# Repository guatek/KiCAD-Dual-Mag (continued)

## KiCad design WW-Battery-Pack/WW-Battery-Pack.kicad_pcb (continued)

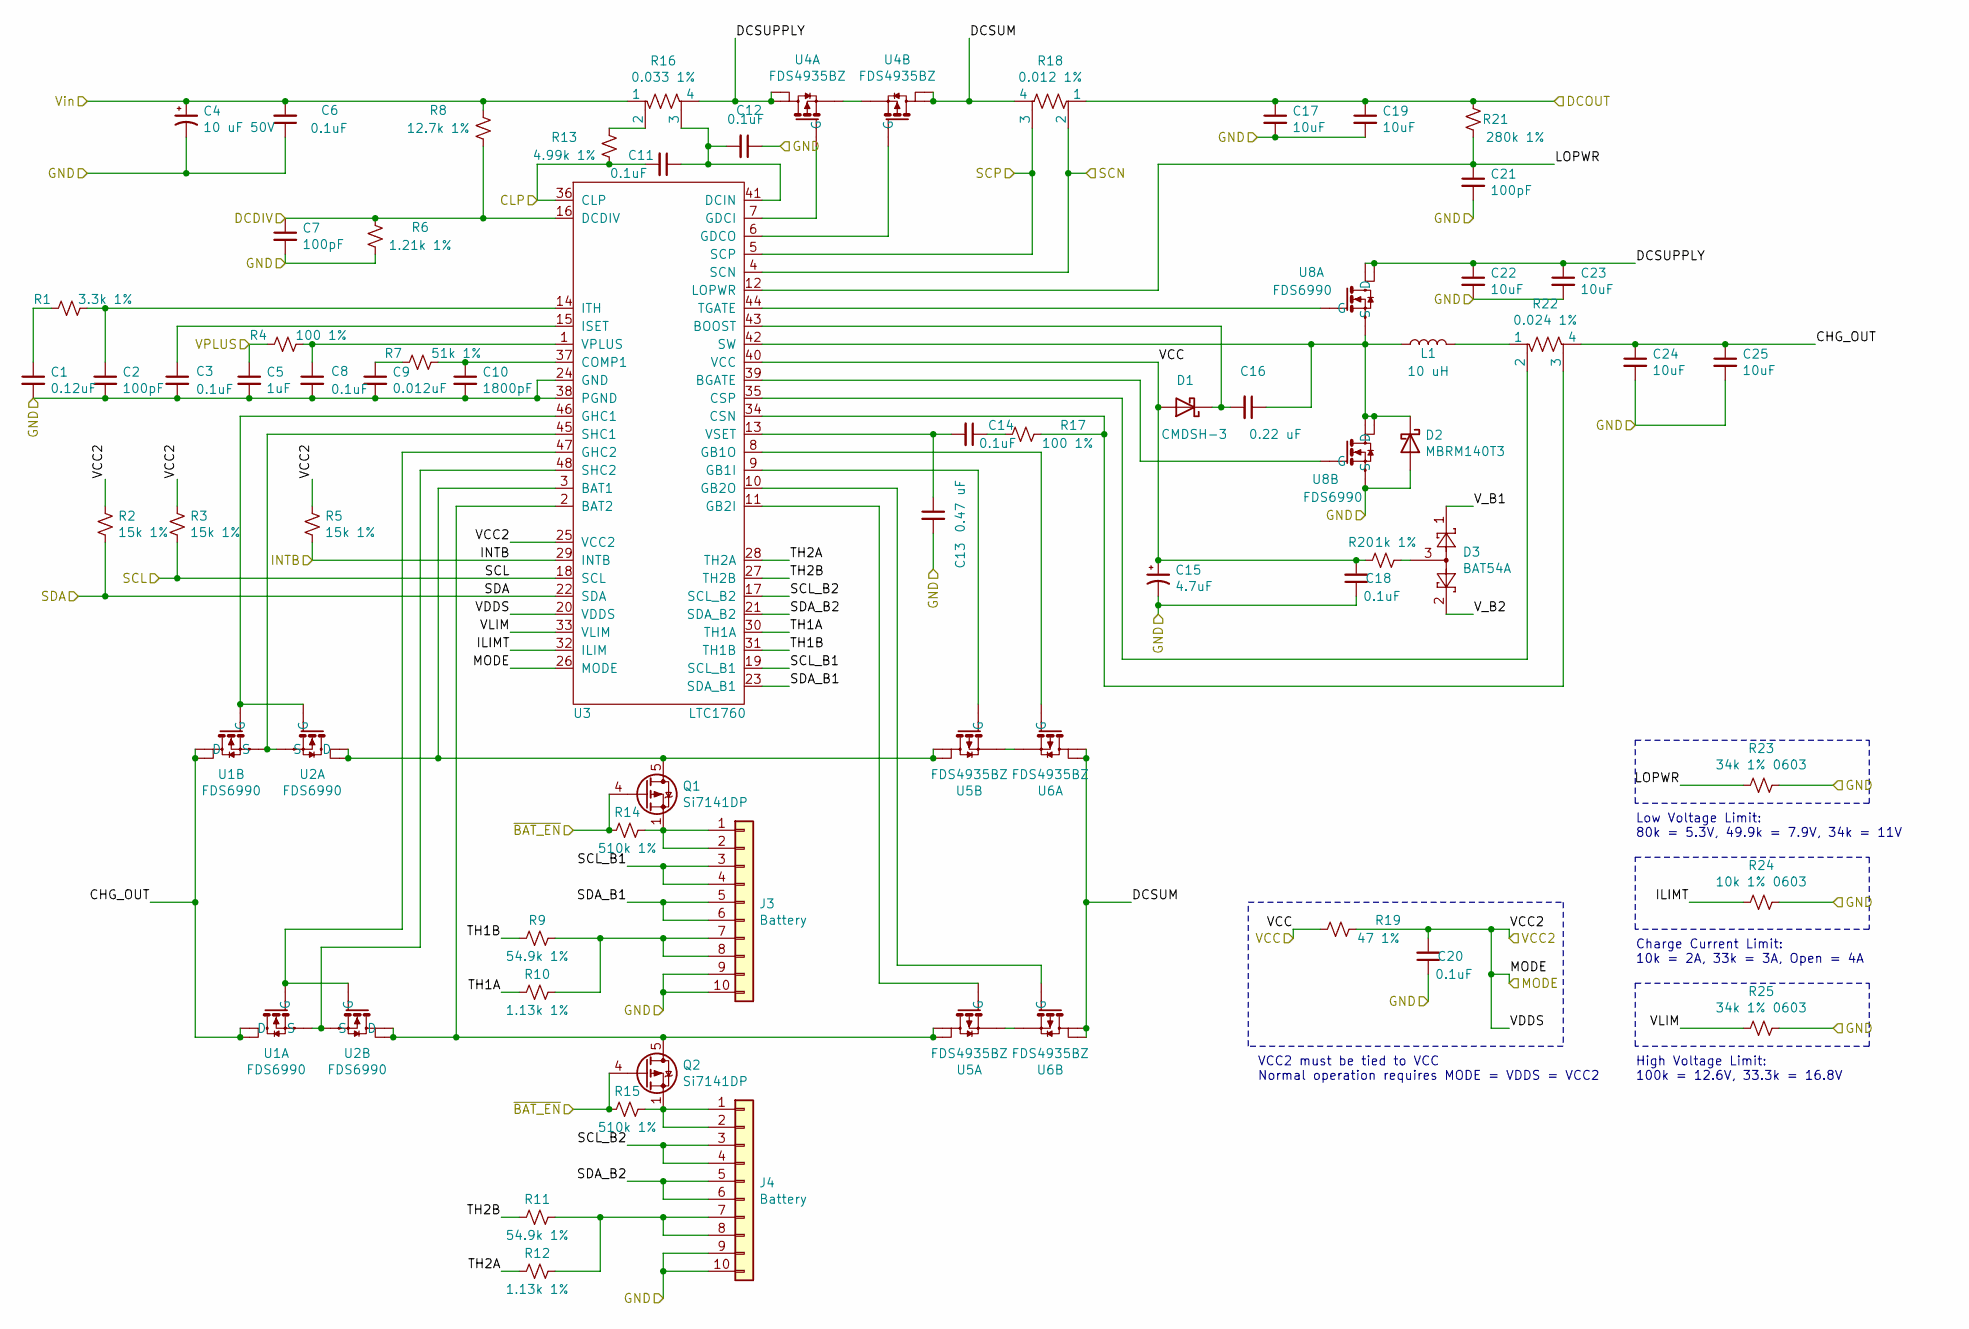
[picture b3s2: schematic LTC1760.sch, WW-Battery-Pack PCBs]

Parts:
C1: 0.12uF; C_0603_1608Metric_Pad1.05x0.95mm_HandSolder; Part Number 399-9962-1-ND
C2, C7, C21: 100pF; C_0603_1608Metric_Pad1.05x0.95mm_HandSolder; Part Number 311-3601-1-ND
C3, C6, C8, C11, C12, C14, C18, C20: 0.1uF; C_0603_1608Metric_Pad1.05x0.95mm_HandSolder; Part Number 490-8020-1-ND
C4: 10 uF 50V; CP_Elec_5x5.3; Part Number PCE3808CT-ND
C5: 1uF; C_0603_1608Metric_Pad1.05x0.95mm_HandSolder; Part Number 478-10073-1-ND
C9: 0.012uF; C_0603_1608Metric_Pad1.05x0.95mm_HandSolder; Part Number 490-16403-1-ND
C10: 1800pF; C_0603_1608Metric_Pad1.05x0.95mm_HandSolder; Part Number 399-7867-1-ND
C13: 0.47 uF; C_0603_1608Metric_Pad1.05x0.95mm_HandSolder; Part Number 478-10368-1-ND
C15: 4.7uF; CP_EIA-3528-15_AVX-H; Part Number 478-3888-1-ND
C16: 0.22 uF; C_0603_1608Metric_Pad1.05x0.95mm_HandSolder; Part Number 478-1243-1-ND
C17, C19, C22, C23, C24, C25: 10uF; C_1206_3216Metric_Pad1.42x1.75mm_HandSolder; Part Number 587-5960-1-ND
D1: CMDSH-3; D_SOD-323; Part Number 1514-CMDSH-3TRPBFREECT-ND
D2: MBRM140T3; D_Powermite_AK; Part Number MBRM140T3GOSCT-ND
D3: BAT54A; SOT-23; Part Number BAT54ACT-ND
J3, J4: Battery; S9169-ND; Part Number SAM10310-ND
L1: 10 uH; L_Bourns_SRR1260; Part Number SRR1260-100MCT-ND
Q1, Q2: Si7141DP; PowerPAK_SO-8_Single; Part Number SI7145DP-T1-GE3CT-ND
R1: 3.3k 1%; R_0603_1608Metric_Pad1.05x0.95mm_HandSolder; Part Number P3.30KHCT-ND
R2, R3, R5: 15k 1%; R_0603_1608Metric_Pad1.05x0.95mm_HandSolder; Part Number P15.0KHCT-ND
R4, R17: 100 1%; R_0603_1608Metric_Pad1.05x0.95mm_HandSolder; Part Number P100HCT-ND
R6: 1.21k 1%; R_0603_1608Metric_Pad1.05x0.95mm_HandSolder; Part Number P1.21KHCT-ND
R7: 51k 1%; R_0603_1608Metric_Pad1.05x0.95mm_HandSolder; Part Number P51.0KHCT-ND
R8: 12.7k 1%; R_0603_1608Metric_Pad1.05x0.95mm_HandSolder; Part Number P12.7KHCT-ND
R9, R11: 54.9k 1%; R_0603_1608Metric_Pad1.05x0.95mm_HandSolder; Part Number P54.9KHCT-ND
R10, R12: 1.13k 1%; R_0603_1608Metric_Pad1.05x0.95mm_HandSolder; Part Number P1.13KLCT-ND
R13: 4.99k 1%; R_0603_1608Metric_Pad1.05x0.95mm_HandSolder; Part Number P4.99KHCT-ND
R14, R15: 510k 1%; R_0603_1608Metric_Pad1.05x0.95mm_HandSolder; Part Number P510KHCT-ND
R16: 0.033 1%; Ohmite_LVK12_1234; Part Number LVK12R033DERCT-ND
R18: 0.012 1%; Ohmite_LVK12_1234; Part Number LVK12R012FERCT-ND
R19: 47 1%; R_0603_1608Metric_Pad1.05x0.95mm_HandSolder; Part Number P47.0HCT-ND
R20: 1k 1%; R_0603_1608Metric_Pad1.05x0.95mm_HandSolder; Part Number P1.00KHCT-ND
R21: 280k 1%; R_0603_1608Metric_Pad1.05x0.95mm_HandSolder; Part Number P280KHCT-ND
R22: 0.024 1%; Ohmite_LVK12_1234; Part Number LVK12R024FERCT-ND
R23, R25: 34k 1% 0603; R_0603_1608Metric_Pad1.05x0.95mm_HandSolder; Part Number P34.0KHCT-ND
R24: 10k 1% 0603; R_0603_1608Metric_Pad1.05x0.95mm_HandSolder; Part Number P10.0KHCT-ND
U1, U8: FDS6990; SO-8_3.9x4.9mm_P1.27mm; Part Number FDS6990ACT-ND
U2: FDS6990; SO-8_3.9x4.9mm_P1.27mm
U3: LTC1760; TSSOP-48_6.1x12.5mm_P0.5mm
U4, U5, U6: FDS4935BZ; SO-8_3.9x4.9mm_P1.27mm; Part Number FDS4935BZCT-ND

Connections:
/GND: C1.2, C2.2, C3.2, C4.2, C5.2, C6.1, C7.2, C8.2, C9.2, C10.2, C12.1, C13.2, C15.2, C17.2, C18.1, C19.2, C20.1, C21.2, C22.2, C23.2, C24.2, C25.2, D2.2 (A), J3.9, J3.10, J4.9, J4.10, R6.1, R23.1, R24.1, R25.1, U3.24 (GND), U3.38 (PGND), U8.3 (S); also elsewhere on the board
/LTC1670_C/CLP: C11.2, R13.1, U3.36 (CLP); also elsewhere on the board
/LTC1670_C/DCDIV: C7.1, R6.2, R8.1, U3.16 (DCDIV); also elsewhere on the board
/LTC1670_C/MODE: C20.2, R2.1, R3.1, R5.1, R19.1, U3.20 (VDDS), U3.25 (VCC2), U3.26 (MODE); also elsewhere on the board
/LTC1670_C/SCN: R18.2, U3.4 (SCN); also elsewhere on the board
/LTC1670_C/SCP: R18.3, U3.5 (SCP); also elsewhere on the board
/LTC1670_C/VCC: C15.1, C18.2, D1.2 (A), R19.2, R20.2, U3.40 (VCC); also elsewhere on the board
/LTC1670_C/VPLUS: C5.1, R4.2; also elsewhere on the board
/LTC1670_C/Vin: C4.1, C6.2, R8.2, R16.1; also elsewhere on the board
/LTC1670_C/~BAT_EN: Q1.4 (G), Q2.4 (G), R14.2, R15.2; also elsewhere on the board
/LTC1760_A/CHG_OUT: C24.1, C25.1, R22.4, U1.5 (D), U1.6 (D), U1.7 (D), U1.8 (D)
/LTC1760_A/DCOUT: C17.1, C19.1, R18.1, R21.2; also elsewhere on the board
/LTC1760_A/DCSUM: R18.4, U4.5 (D), U4.6 (D), U6.5 (D), U6.6 (D), U6.7 (D), U6.8 (D)
/LTC1760_A/DCSUPPLY: C22.1, C23.1, R16.4, U4.7 (D), U4.8 (D), U8.7 (D), U8.8 (D)
/LTC1760_A/ILIMT: R24.2, U3.32 (ILIM)
/LTC1760_A/INTB: R5.2, U3.29 (INTB)
/LTC1760_A/LOPWR: C21.1, R21.1, R23.2, U3.12 (LOPWR)
/LTC1760_A/SCL: R3.2, U3.18 (SCL)
/LTC1760_A/SCL_B1: J3.3, J3.4, U3.19 (SCL_B1)
/LTC1760_A/SCL_B2: J4.3, J4.4, U3.17 (SCL_B2)
/LTC1760_A/SDA: R2.2, U3.22 (SDA)
/LTC1760_A/SDA_B1: J3.5, J3.6, U3.23 (SDA_B1)
/LTC1760_A/SDA_B2: J4.5, J4.6, U3.21 (SDA_B2)
/LTC1760_A/TH1A: R10.2, U3.30 (TH1A)
/LTC1760_A/TH1B: R9.2, U3.31 (TH1B)
/LTC1760_A/TH2A: R12.2, U3.28 (TH2A)
/LTC1760_A/TH2B: R11.2, U3.27 (TH2B)
/LTC1760_A/VLIM: R25.2, U3.33 (VLIM)
/LTC1760_A/V_B1: D3.1
/LTC1760_A/V_B2: D3.2
unnamed: C1.1, R1.2
unnamed: C2.1, R1.1, U3.14 (ITH)
unnamed: C3.1, U3.15 (ISET)
unnamed: C8.1, R4.1, U3.1 (VPLUS)
unnamed: C9.1, R7.2
unnamed: C10.1, R7.1, U3.37 (COMP1)
unnamed: C11.1, C12.2, R16.3, U3.41 (DCIN)
unnamed: C13.1, C14.2, U3.13 (VSET)
unnamed: C14.1, R17.2
unnamed: C16.1, D2.1 (K), L1.1, U3.42 (SW), U8.1 (S), U8.5 (D), U8.6 (D)
unnamed: C16.2, D1.1 (K), U3.43 (BOOST)
unnamed: D3.3, R20.1
unnamed: J3.1, J3.2, Q1.1 (S), Q1.2 (S), Q1.3 (S), R14.1
unnamed: J3.7, J3.8, R9.1, R10.1
unnamed: J4.1, J4.2, Q2.1 (S), Q2.2 (S), Q2.3 (S), R15.1
unnamed: J4.7, J4.8, R11.1, R12.1
unnamed: L1.2, R22.1
unnamed: Q1.5 (D), U2.7 (D), U2.8 (D), U3.3 (BAT1), U5.5 (D), U5.6 (D)
unnamed: Q2.5 (D), U2.5 (D), U2.6 (D), U3.2 (BAT2), U5.7 (D), U5.8 (D)
unnamed: R13.2, R16.2
unnamed: R17.1, R22.3, U3.34 (CSN)
unnamed: R22.2, U3.35 (CSP)
unnamed: U1.1 (S), U2.3 (S), U3.48 (SHC2)
unnamed: U1.2 (G), U2.4 (G), U3.47 (GHC2)
unnamed: U1.3 (S), U2.1 (S), U3.45 (SHC1)
unnamed: U1.4 (G), U2.2 (G), U3.46 (GHC1)
unnamed: U3.6 (GDCO), U4.4 (G)
unnamed: U3.7 (GDCI), U4.2 (G)
unnamed: U3.8 (GB1O), U6.2 (G)
unnamed: U3.9 (GB1I), U5.4 (G)
unnamed: U3.10 (GB2O), U6.4 (G)
unnamed: U3.11 (GB2I), U5.2 (G)
unnamed: U3.39 (BGATE), U8.4 (G)
unnamed: U3.44 (TGATE), U8.2 (G)
unnamed: U4.1 (S), U4.3 (S)
unnamed: U5.1 (S), U6.3 (S)
unnamed: U5.3 (S), U6.1 (S)

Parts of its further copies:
C32, C57: 0.12uF; C_0603_1608Metric_Pad1.05x0.95mm_HandSolder; Part Number 399-9962-1-ND
C33, C38, C52, C58, C63, C77: 100pF; C_0603_1608Metric_Pad1.05x0.95mm_HandSolder; Part Number 311-3601-1-ND
C34, C37, C39, C42, C43, C45, C49, C51, C59, C62, C64, C67, C68, C70, C74, C76: 0.1uF; C_0603_1608Metric_Pad1.05x0.95mm_HandSolder; Part Number 490-8020-1-ND
C35, C60: 10 uF 50V; CP_Elec_5x5.3; Part Number PCE3808CT-ND
C36, C61: 1uF; C_0603_1608Metric_Pad1.05x0.95mm_HandSolder; Part Number 478-10073-1-ND
C40, C65: 0.012uF; C_0603_1608Metric_Pad1.05x0.95mm_HandSolder; Part Number 490-16403-1-ND
C41, C66: 1800pF; C_0603_1608Metric_Pad1.05x0.95mm_HandSolder; Part Number 399-7867-1-ND
C44, C69: 0.47 uF; C_0603_1608Metric_Pad1.05x0.95mm_HandSolder; Part Number 478-10368-1-ND
C46, C71: 4.7uF; CP_EIA-3528-15_AVX-H; Part Number 478-3888-1-ND
C47, C72: 0.22 uF; C_0603_1608Metric_Pad1.05x0.95mm_HandSolder; Part Number 478-1243-1-ND
C48, C50, C53, C54, C55, C56, C73, C75, C78, C79, C80, C81: 10uF; C_1206_3216Metric_Pad1.42x1.75mm_HandSolder; Part Number 587-5960-1-ND
D4, D7: CMDSH-3; D_SOD-323; Part Number 1514-CMDSH-3TRPBFREECT-ND
D5, D8: MBRM140T3; D_Powermite_AK; Part Number MBRM140T3GOSCT-ND
D6, D9: BAT54A; SOT-23; Part Number BAT54ACT-ND
J5, J6, J7, J8: Battery; S9169-ND; Part Number SAM10310-ND
L2, L3: 10 uH; L_Bourns_SRR1260; Part Number SRR1260-100MCT-ND
Q6, Q7, Q8, Q9: Si7141DP; PowerPAK_SO-8_Single; Part Number SI7145DP-T1-GE3CT-ND
R29, R54: 3.3k 1%; R_0603_1608Metric_Pad1.05x0.95mm_HandSolder; Part Number P3.30KHCT-ND
R30, R31, R33, R55, R56, R58: 15k 1%; R_0603_1608Metric_Pad1.05x0.95mm_HandSolder; Part Number P15.0KHCT-ND
R32, R45, R57, R70: 100 1%; R_0603_1608Metric_Pad1.05x0.95mm_HandSolder; Part Number P100HCT-ND
R34, R59: 1.21k 1%; R_0603_1608Metric_Pad1.05x0.95mm_HandSolder; Part Number P1.21KHCT-ND
R35, R60: 51k 1%; R_0603_1608Metric_Pad1.05x0.95mm_HandSolder; Part Number P51.0KHCT-ND
R36, R61: 12.7k 1%; R_0603_1608Metric_Pad1.05x0.95mm_HandSolder; Part Number P12.7KHCT-ND
R37, R39, R62, R64: 54.9k 1%; R_0603_1608Metric_Pad1.05x0.95mm_HandSolder; Part Number P54.9KHCT-ND
R38, R40, R63, R65: 1.13k 1%; R_0603_1608Metric_Pad1.05x0.95mm_HandSolder; Part Number P1.13KLCT-ND
R41, R66: 4.99k 1%; R_0603_1608Metric_Pad1.05x0.95mm_HandSolder; Part Number P4.99KHCT-ND
R42, R43, R67, R68: 510k 1%; R_0603_1608Metric_Pad1.05x0.95mm_HandSolder; Part Number P510KHCT-ND
R44, R69: 0.033 1%; Ohmite_LVK12_1234; Part Number LVK12R033DERCT-ND
R46, R71: 0.012 1%; Ohmite_LVK12_1234; Part Number LVK12R012FERCT-ND
R47, R72: 47 1%; R_0603_1608Metric_Pad1.05x0.95mm_HandSolder; Part Number P47.0HCT-ND
R48, R73: 1k 1%; R_0603_1608Metric_Pad1.05x0.95mm_HandSolder; Part Number P1.00KHCT-ND
R49, R74: 280k 1%; R_0603_1608Metric_Pad1.05x0.95mm_HandSolder; Part Number P280KHCT-ND
R50, R75: 0.024 1%; Ohmite_LVK12_1234; Part Number LVK12R024FERCT-ND
R51, R53, R76, R78: 34k 1% 0603; R_0603_1608Metric_Pad1.05x0.95mm_HandSolder; Part Number P34.0KHCT-ND
R52, R77: 10k 1% 0603; R_0603_1608Metric_Pad1.05x0.95mm_HandSolder; Part Number P10.0KHCT-ND
U12, U17, U18, U24, U25: FDS6990; SO-8_3.9x4.9mm_P1.27mm; Part Number FDS6990ACT-ND
U13, U20: LTC1760; TSSOP-48_6.1x12.5mm_P0.5mm
U15, U16, U21, U22, U23: FDS4935BZ; SO-8_3.9x4.9mm_P1.27mm; Part Number FDS4935BZCT-ND
U19: FDS6990; SO-8_3.9x4.9mm_P1.27mm

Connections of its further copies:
/GND: C32.2, C33.2, C34.2, C35.2, C36.2, C37.1, C38.2, C39.2, C40.2, C41.2, C43.1, C44.2, C46.2, C48.2, C49.1, C50.2, C51.1, C52.2, C53.2, C54.2, C55.2, C56.2, C57.2, C58.2, C59.2, C60.2, C61.2, C62.1, C63.2, C64.2, C65.2, C66.2, C68.1, C69.2, C71.2, C73.2, C74.1, C75.2, C76.1, C77.2, C78.2, C79.2, C80.2, C81.2, D5.2 (A), D8.2 (A), J5.9, J5.10, J6.9, J6.10, J7.9, J7.10, J8.9, J8.10, R34.1, R51.1, R52.1, R53.1, R59.1, R76.1, R77.1, R78.1, U13.24 (GND), U13.38 (PGND), U17.3 (S), U20.24 (GND), U20.38 (PGND), U24.3 (S); also elsewhere on the board
/LTC1670_C/CHG_OUT: C80.1, C81.1, R75.4, U18.5 (D), U18.6 (D), U18.7 (D), U18.8 (D)
/LTC1670_C/CLP: C42.2, C67.2, R41.1, R66.1, U13.36 (CLP), U20.36 (CLP); also elsewhere on the board
/LTC1670_C/DCDIV: C38.1, C63.1, R34.2, R36.1, R59.2, R61.1, U13.16 (DCDIV), U20.16 (DCDIV); also elsewhere on the board
/LTC1670_C/DCOUT: C73.1, C75.1, R71.1, R74.2; also elsewhere on the board
/LTC1670_C/DCSUM: R71.4, U21.5 (D), U21.6 (D), U23.5 (D), U23.6 (D), U23.7 (D), U23.8 (D)
/LTC1670_C/DCSUPPLY: C78.1, C79.1, R69.4, U21.7 (D), U21.8 (D), U24.7 (D), U24.8 (D)
/LTC1670_C/ILIMT: R77.2, U20.32 (ILIM)
/LTC1670_C/INTB: R58.2, U20.29 (INTB)
/LTC1670_C/LOPWR: C77.1, R74.1, R76.2, U20.12 (LOPWR)
/LTC1670_C/MODE: C51.2, C76.2, R30.1, R31.1, R33.1, R47.1, R55.1, R56.1, R58.1, R72.1, U13.20 (VDDS), U13.25 (VCC2), U13.26 (MODE), U20.20 (VDDS), U20.25 (VCC2), U20.26 (MODE); also elsewhere on the board
/LTC1670_C/SCL: R56.2, U20.18 (SCL)
/LTC1670_C/SCL_B1: J7.3, J7.4, U20.19 (SCL_B1)
/LTC1670_C/SCL_B2: J8.3, J8.4, U20.17 (SCL_B2)
/LTC1670_C/SCN: R46.2, R71.2, U13.4 (SCN), U20.4 (SCN); also elsewhere on the board
/LTC1670_C/SCP: R46.3, R71.3, U13.5 (SCP), U20.5 (SCP); also elsewhere on the board
/LTC1670_C/SDA: R55.2, U20.22 (SDA)
/LTC1670_C/SDA_B1: J7.5, J7.6, U20.23 (SDA_B1)
/LTC1670_C/SDA_B2: J8.5, J8.6, U20.21 (SDA_B2)
/LTC1670_C/TH1A: R63.2, U20.30 (TH1A)
/LTC1670_C/TH1B: R62.2, U20.31 (TH1B)
/LTC1670_C/TH2A: R65.2, U20.28 (TH2A)
/LTC1670_C/TH2B: R64.2, U20.27 (TH2B)
/LTC1670_C/VCC: C46.1, C49.2, C71.1, C74.2, D4.2 (A), D7.2 (A), R47.2, R48.2, R72.2, R73.2, U13.40 (VCC), U20.40 (VCC); also elsewhere on the board
/LTC1670_C/VLIM: R78.2, U20.33 (VLIM)
/LTC1670_C/VPLUS: C36.1, C61.1, R32.2, R57.2; also elsewhere on the board
/LTC1670_C/V_B1: D9.1
/LTC1670_C/V_B2: D9.2
/LTC1670_C/Vin: C35.1, C37.2, C60.1, C62.2, R36.2, R44.1, R61.2, R69.1; also elsewhere on the board
/LTC1670_C/~BAT_EN: Q6.4 (G), Q7.4 (G), Q8.4 (G), Q9.4 (G), R42.2, R43.2, R67.2, R68.2; also elsewhere on the board
/LTC1760_B/CHG_OUT: C55.1, C56.1, R50.4; also elsewhere on the board
/LTC1760_B/DCOUT: C48.1, C50.1, R46.1, R49.2; also elsewhere on the board
/LTC1760_B/DCSUM: R46.4, U16.5 (D), U16.6 (D), U16.7 (D), U16.8 (D); also elsewhere on the board
/LTC1760_B/DCSUPPLY: C53.1, C54.1, R44.4, U17.7 (D), U17.8 (D); also elsewhere on the board
/LTC1760_B/ILIMT: R52.2, U13.32 (ILIM)
/LTC1760_B/INTB: R33.2, U13.29 (INTB)
/LTC1760_B/LOPWR: C52.1, R49.1, R51.2, U13.12 (LOPWR)
/LTC1760_B/SCL: R31.2, U13.18 (SCL)
/LTC1760_B/SCL_B1: J5.3, J5.4, U13.19 (SCL_B1)
/LTC1760_B/SCL_B2: J6.3, J6.4, U13.17 (SCL_B2)
/LTC1760_B/SDA: R30.2, U13.22 (SDA)
/LTC1760_B/SDA_B1: J5.5, J5.6, U13.23 (SDA_B1)
/LTC1760_B/SDA_B2: J6.5, J6.6, U13.21 (SDA_B2)
/LTC1760_B/TH1A: R38.2, U13.30 (TH1A)
/LTC1760_B/TH1B: R37.2, U13.31 (TH1B)
/LTC1760_B/TH2A: R40.2, U13.28 (TH2A)
/LTC1760_B/TH2B: R39.2, U13.27 (TH2B)
/LTC1760_B/VLIM: R53.2, U13.33 (VLIM)
/LTC1760_B/V_B1: D6.1
/LTC1760_B/V_B2: D6.2
unnamed: C32.1, R29.2
unnamed: C33.1, R29.1, U13.14 (ITH)
unnamed: C34.1, U13.15 (ISET)
unnamed: C39.1, R32.1, U13.1 (VPLUS)
unnamed: C40.1, R35.2
unnamed: C41.1, R35.1, U13.37 (COMP1)
unnamed: C42.1, C43.2, R44.3, U13.41 (DCIN)
unnamed: C44.1, C45.2, U13.13 (VSET)
unnamed: C45.1, R45.2
unnamed: C47.1, D5.1 (K), L2.1, U13.42 (SW), U17.1 (S), U17.5 (D), U17.6 (D)
unnamed: C47.2, D4.1 (K), U13.43 (BOOST)
unnamed: C57.1, R54.2
unnamed: C58.1, R54.1, U20.14 (ITH)
unnamed: C59.1, U20.15 (ISET)
unnamed: C64.1, R57.1, U20.1 (VPLUS)
unnamed: C65.1, R60.2
unnamed: C66.1, R60.1, U20.37 (COMP1)
unnamed: C67.1, C68.2, R69.3, U20.41 (DCIN)
unnamed: C69.1, C70.2, U20.13 (VSET)
unnamed: C70.1, R70.2
unnamed: C72.1, D8.1 (K), L3.1, U20.42 (SW), U24.1 (S), U24.5 (D), U24.6 (D)
unnamed: C72.2, D7.1 (K), U20.43 (BOOST)
unnamed: D6.3, R48.1
unnamed: D9.3, R73.1
unnamed: J5.1, J5.2, Q6.1 (S), Q6.2 (S), Q6.3 (S), R42.1
unnamed: J5.7, J5.8, R37.1, R38.1
unnamed: J6.1, J6.2, Q7.1 (S), Q7.2 (S), Q7.3 (S), R43.1
unnamed: J6.7, J6.8, R39.1, R40.1
unnamed: J7.1, J7.2, Q8.1 (S), Q8.2 (S), Q8.3 (S), R67.1
unnamed: J7.7, J7.8, R62.1, R63.1
unnamed: J8.1, J8.2, Q9.1 (S), Q9.2 (S), Q9.3 (S), R68.1
unnamed: J8.7, J8.8, R64.1, R65.1
unnamed: L2.2, R50.1
unnamed: L3.2, R75.1
unnamed: Q6.5 (D), U12.7 (D), U12.8 (D), U13.3 (BAT1), U15.5 (D), U15.6 (D)
unnamed: Q7.5 (D), U12.5 (D), U12.6 (D), U13.2 (BAT2), U15.7 (D), U15.8 (D)
unnamed: Q8.5 (D), U19.7 (D), U19.8 (D), U20.3 (BAT1), U22.5 (D), U22.6 (D)
unnamed: Q9.5 (D), U19.5 (D), U19.6 (D), U20.2 (BAT2), U22.7 (D), U22.8 (D)
unnamed: R41.2, R44.2
unnamed: R45.1, R50.3, U13.34 (CSN)
unnamed: R50.2, U13.35 (CSP)
unnamed: R66.2, R69.2
unnamed: R70.1, R75.3, U20.34 (CSN)
unnamed: R75.2, U20.35 (CSP)
unnamed 186: U12.1 (S), U13.45 (SHC1); also elsewhere on the board
unnamed 187: U12.2 (G), U13.46 (GHC1); also elsewhere on the board
unnamed 188: U12.3 (S), U13.48 (SHC2); also elsewhere on the board
unnamed 189: U12.4 (G), U13.47 (GHC2); also elsewhere on the board
unnamed 190: U13.6 (GDCO); also elsewhere on the board
unnamed 191: U13.7 (GDCI); also elsewhere on the board
unnamed: U13.8 (GB1O), U16.2 (G)
unnamed: U13.9 (GB1I), U15.4 (G)
unnamed: U13.10 (GB2O), U16.4 (G)
unnamed: U13.11 (GB2I), U15.2 (G)
unnamed: U13.39 (BGATE), U17.4 (G)
unnamed: U13.44 (TGATE), U17.2 (G)
unnamed: U15.1 (S), U16.3 (S)
unnamed: U15.3 (S), U16.1 (S)
unnamed: U18.1 (S), U19.3 (S), U20.48 (SHC2)
unnamed: U18.2 (G), U19.4 (G), U20.47 (GHC2)
unnamed: U18.3 (S), U19.1 (S), U20.45 (SHC1)
unnamed: U18.4 (G), U19.2 (G), U20.46 (GHC1)
unnamed: U20.6 (GDCO), U21.4 (G)
unnamed: U20.7 (GDCI), U21.2 (G)
unnamed: U20.8 (GB1O), U23.2 (G)
unnamed: U20.9 (GB1I), U22.4 (G)
unnamed: U20.10 (GB2O), U23.4 (G)
unnamed: U20.11 (GB2I), U22.2 (G)
unnamed: U20.39 (BGATE), U24.4 (G)
unnamed: U20.44 (TGATE), U24.2 (G)
unnamed: U21.1 (S), U21.3 (S)
unnamed: U22.1 (S), U23.3 (S)
unnamed: U22.3 (S), U23.1 (S)

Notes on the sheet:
Charge Current Limit: 10k = 2A, 33k = 3A, Open = 4A
Low Voltage Limit: 80k = 5.3V, 49.9k = 7.9V, 34k = 11V
High Voltage Limit: 100k = 12.6V, 33.3k = 16.8V
VCC2 must be tied to VCC Normal operation requires MODE = VDDS = VCC2

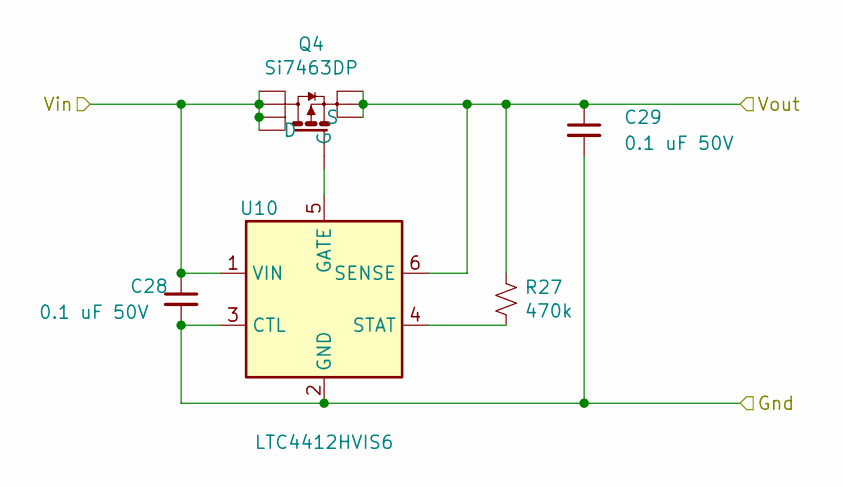
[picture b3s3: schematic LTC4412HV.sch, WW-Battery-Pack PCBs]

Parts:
C26, C27: 0.1 uF 50V; C_0603_1608Metric_Pad1.05x0.95mm_HandSolder; Part Number C0603C104M5RACTU
Q3: Si7463DP; PowerPAK_SO-8_Single; Part Number SI7463DP-T1-E3CT-ND
R26: 470k; R_0603_1608Metric_Pad1.05x0.95mm_HandSolder; Part Number CPF0603B470KE1
U9: LTC4412HVIS6; TSOT-23-6; Part Number LTC4412HVIS6#TRPBF

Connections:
/GND: C26.2, C27.2, U9.2 (GND), U9.3 (CTL); also elsewhere on the board
/LTC1760_A/DCOUT: C26.1, Q3.5 (D), U9.1 (VIN); also elsewhere on the board
/sheet6090344F/Vout: C27.1, Q3.1 (S), Q3.2 (S), Q3.3 (S), R26.1, U9.6 (SENSE); also elsewhere on the board
unnamed: Q3.4 (G), U9.5 (GATE)
unnamed: R26.2, U9.4 (STAT)

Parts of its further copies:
C28, C29, C30, C31: 0.1 uF 50V; C_0603_1608Metric_Pad1.05x0.95mm_HandSolder; Part Number C0603C104M5RACTU
Q4, Q5: Si7463DP; PowerPAK_SO-8_Single; Part Number SI7463DP-T1-E3CT-ND
R27, R28: 470k; R_0603_1608Metric_Pad1.05x0.95mm_HandSolder; Part Number CPF0603B470KE1
U10, U11: LTC4412HVIS6; TSOT-23-6; Part Number LTC4412HVIS6#TRPBF

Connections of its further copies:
/GND: C28.2, C29.2, C30.2, C31.2, U10.2 (GND), U10.3 (CTL), U11.2 (GND), U11.3 (CTL); also elsewhere on the board
/LTC1670_C/DCOUT: C30.1, Q5.5 (D), U11.1 (VIN); also elsewhere on the board
/LTC1760_B/DCOUT: C28.1, Q4.5 (D), U10.1 (VIN); also elsewhere on the board
/sheet6090344F/Vout: C29.1, C31.1, Q4.1 (S), Q4.2 (S), Q4.3 (S), Q5.1 (S), Q5.2 (S), Q5.3 (S), R27.1, R28.1, U10.6 (SENSE), U11.6 (SENSE); also elsewhere on the board
unnamed: Q4.4 (G), U10.5 (GATE)
unnamed: Q5.4 (G), U11.5 (GATE)
unnamed: R27.2, U10.4 (STAT)
unnamed: R28.2, U11.4 (STAT)

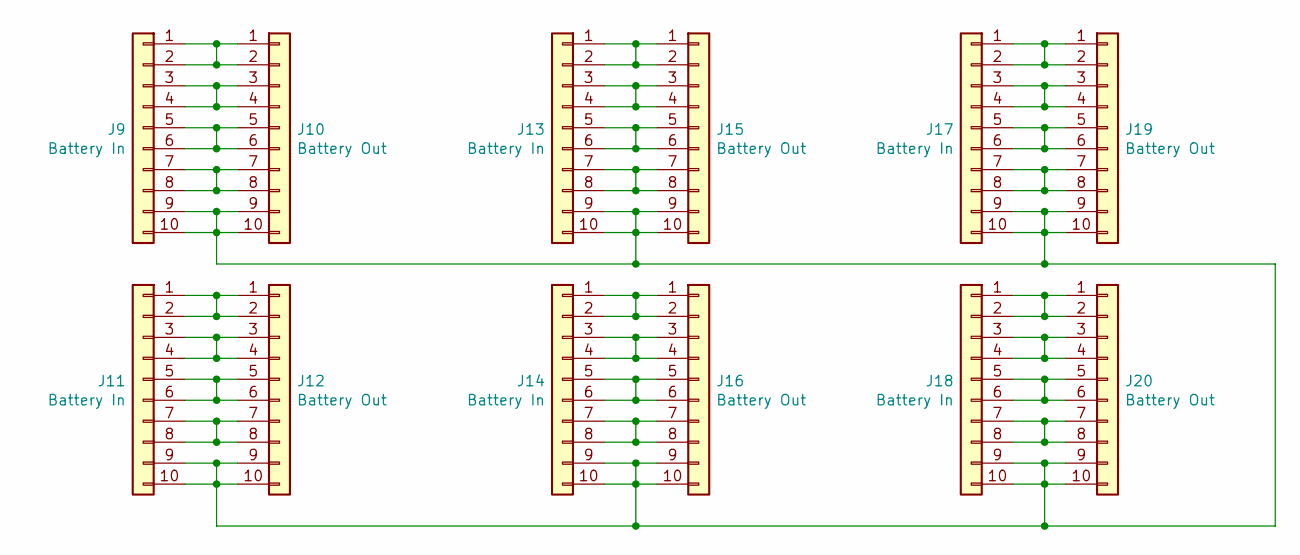
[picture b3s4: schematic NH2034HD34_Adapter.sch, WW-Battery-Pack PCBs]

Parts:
J9, J11, J13, J14, J17, J18: Battery In; NH2034HD34; Part Number 5787446-1-ND
J10, J12, J16, J19, J20: Battery Out; S9194-ND; Part Number S9194-ND
J15: Battery Out; SAM11936-ND; Part Number S9194-ND

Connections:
unnamed: J9.1, J9.2, J10.1, J10.2
unnamed: J9.3, J9.4, J10.3, J10.4
unnamed: J9.5, J9.6, J10.5, J10.6
unnamed: J9.7, J9.8, J10.7, J10.8
unnamed: J9.9, J9.10, J10.9, J10.10, J11.9, J11.10, J12.9, J12.10, J13.9, J13.10, J14.9, J14.10, J15.9, J15.10, J16.9, J16.10, J17.9, J17.10, J18.9, J18.10, J19.9, J19.10, J20.9, J20.10
unnamed: J11.1, J11.2, J12.1, J12.2
unnamed: J11.3, J11.4, J12.3, J12.4
unnamed: J11.5, J11.6, J12.5, J12.6
unnamed: J11.7, J11.8, J12.7, J12.8
unnamed: J13.1, J13.2, J15.1, J15.2
unnamed: J13.3, J13.4, J15.3, J15.4
unnamed: J13.5, J13.6, J15.5, J15.6
unnamed: J13.7, J13.8, J15.7, J15.8
unnamed: J14.1, J14.2, J16.1, J16.2
unnamed: J14.3, J14.4, J16.3, J16.4
unnamed: J14.5, J14.6, J16.5, J16.6
unnamed: J14.7, J14.8, J16.7, J16.8
unnamed: J17.1, J17.2, J19.1, J19.2
unnamed: J17.3, J17.4, J19.3, J19.4
unnamed: J17.5, J17.6, J19.5, J19.6
unnamed: J17.7, J17.8, J19.7, J19.8
unnamed: J18.1, J18.2, J20.1, J20.2
unnamed: J18.3, J18.4, J20.3, J20.4
unnamed: J18.5, J18.6, J20.5, J20.6
unnamed: J18.7, J18.8, J20.7, J20.8

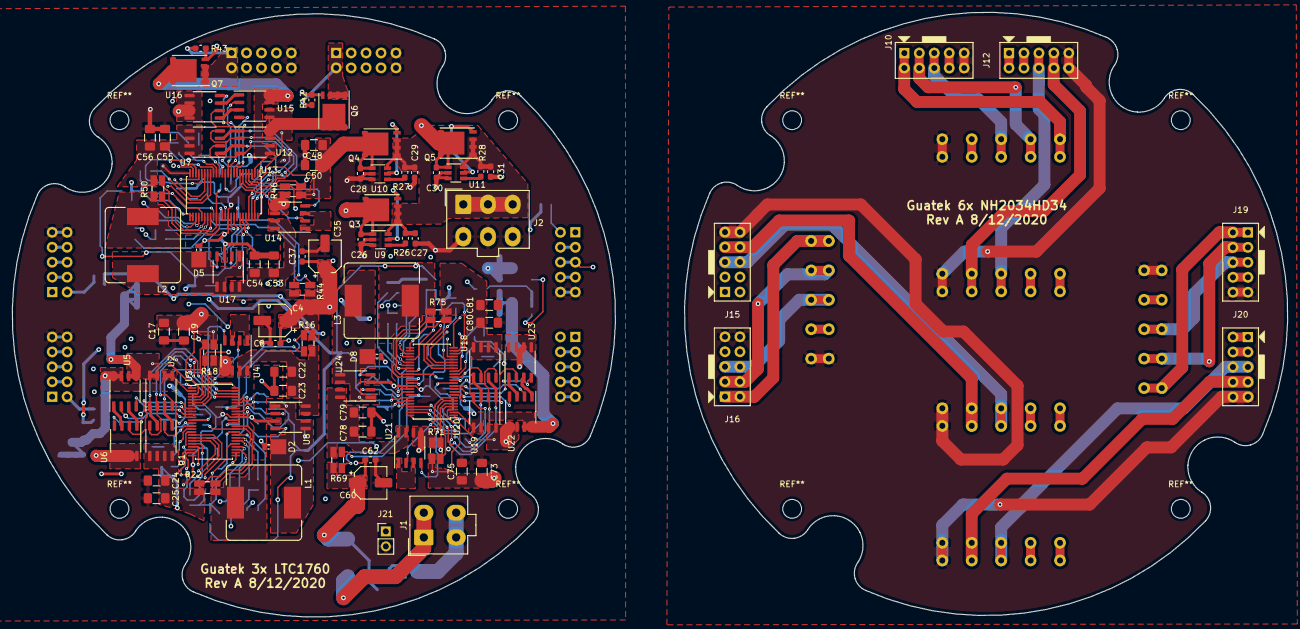
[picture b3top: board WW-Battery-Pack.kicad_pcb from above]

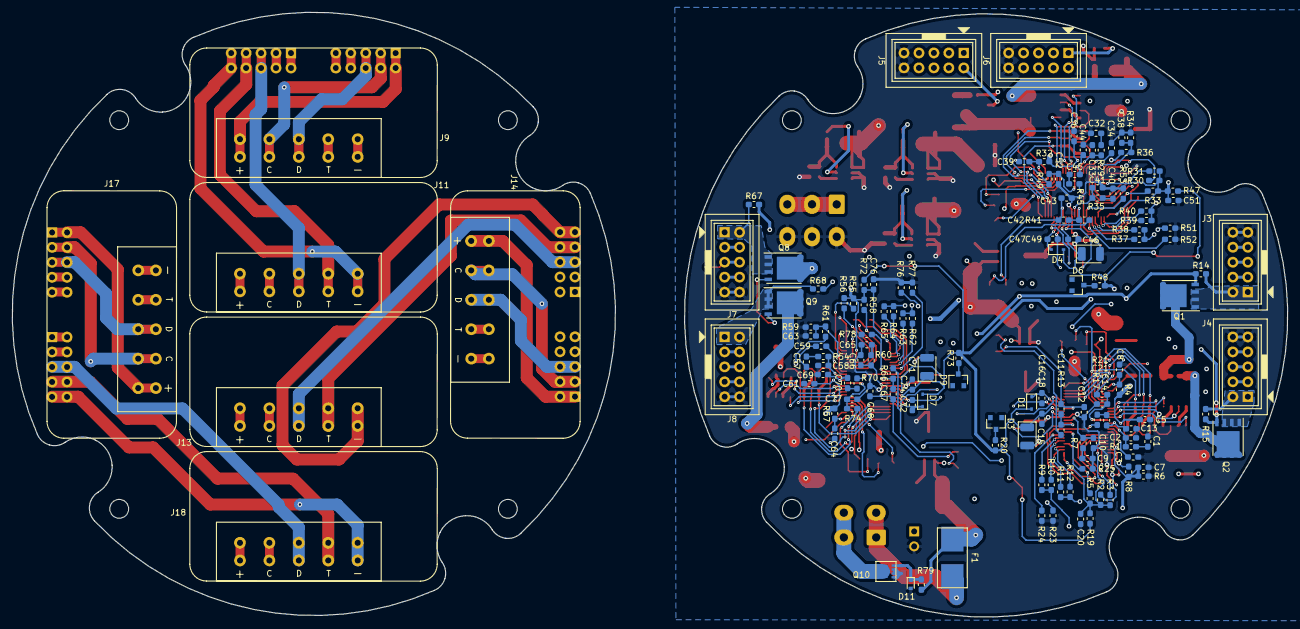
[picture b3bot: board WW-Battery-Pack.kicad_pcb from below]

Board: 4 copper layers, 102.5 x 102.5 mm, 229 parts (141 on the bottom side), 210 nets.

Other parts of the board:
U7: FDS6990; SO-8_3.9x4.9mm_P1.27mm
U14: FDS4935BZ; SO-8_3.9x4.9mm_P1.27mm

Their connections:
/LTC1760_B/CHG_OUT: U7.5, U7.6, U7.7, U7.8; also elsewhere on the board
/LTC1760_B/DCSUM: U14.5, U14.6; also elsewhere on the board
/LTC1760_B/DCSUPPLY: U14.7, U14.8; also elsewhere on the board
unnamed 186: U7.3; also elsewhere on the board
unnamed 187: U7.4; also elsewhere on the board
unnamed 188: U7.1; also elsewhere on the board
unnamed 189: U7.2; also elsewhere on the board
unnamed 190: U14.4; also elsewhere on the board
unnamed 191: U14.2; also elsewhere on the board
unnamed: U14.1, U14.3

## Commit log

2021-01-25 Dual-Mag-01 RevA As Built: Dual-Mag-Strobe Dual-Mag-Camera-Control WW-Battery-Pack
2022-04-06 updated to KiCAD 6.0
2022-07-02 Add files via upload
    Uploaded Rev 2 files
2023-08-23 Moved Connectors, NEW PTC Footprint
    updated ptc footprints to 0603. Relocated GPIO connectors J1-J4
